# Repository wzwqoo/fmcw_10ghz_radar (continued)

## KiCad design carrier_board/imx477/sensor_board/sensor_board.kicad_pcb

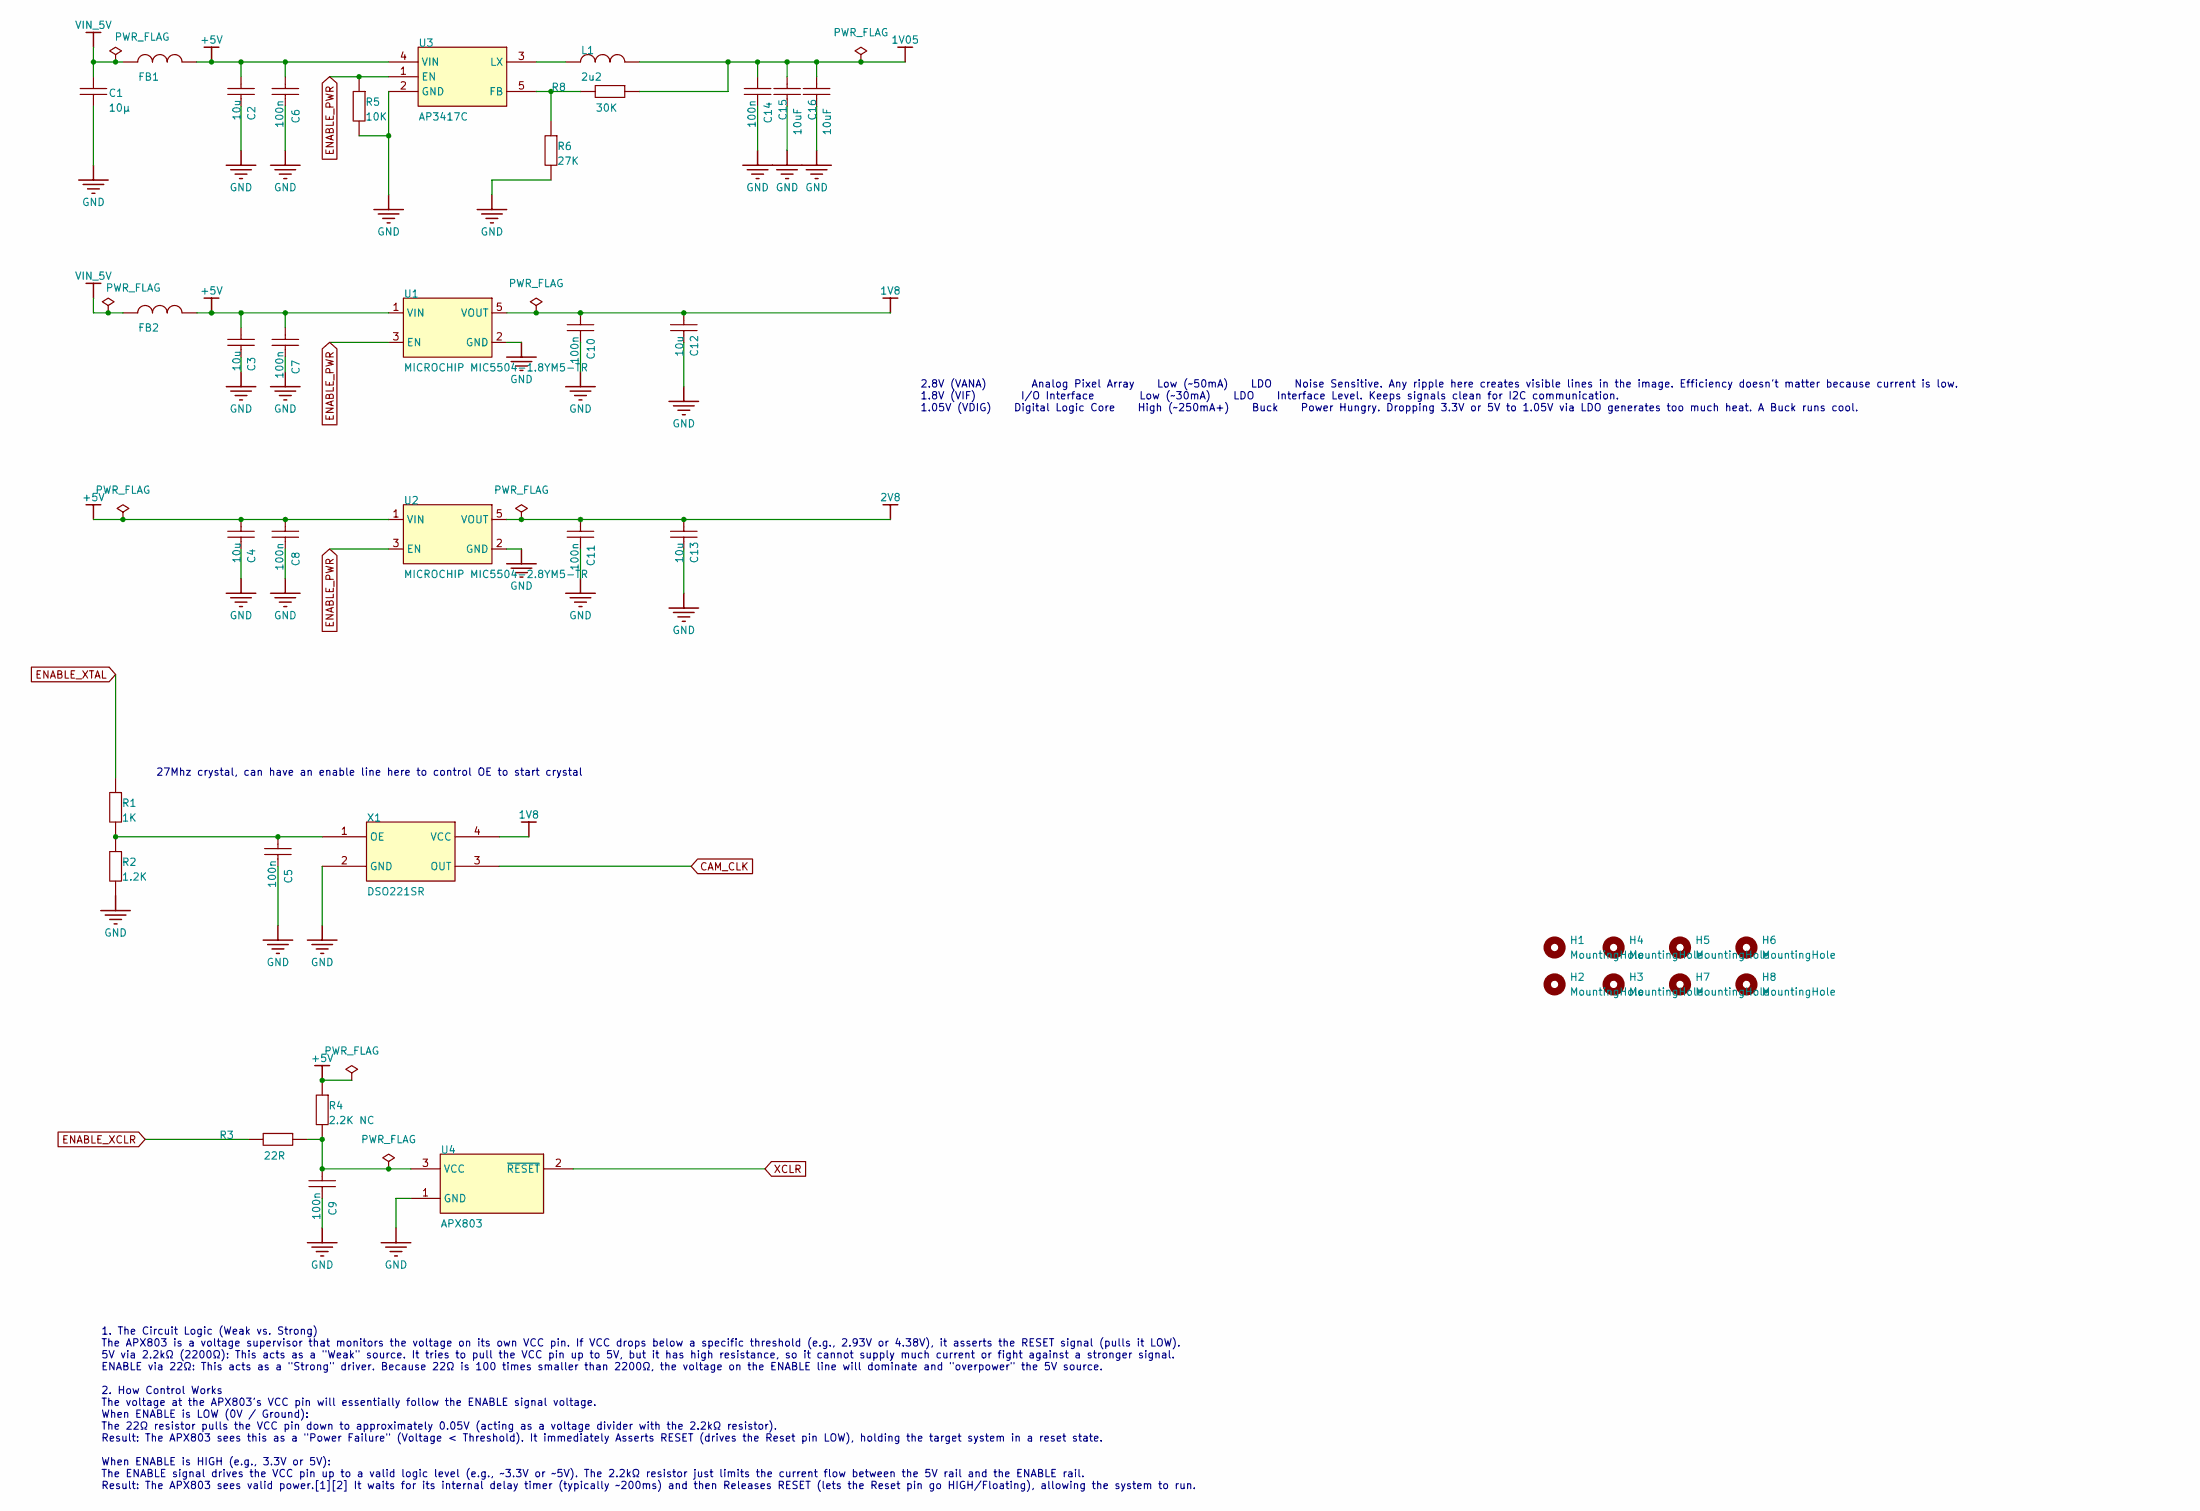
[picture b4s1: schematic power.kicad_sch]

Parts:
C1: 10uF; C_0805_2012Metric; TOLERANCE ±20%; RATINGS 50V; X5R; MANUFACTURER PART NUMBE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 UMK325BJ106MM-T; LCSC Part # C88484
C2, C3, C4, C12, C13: 10uF; C_0805_2012Metric; RATINGS 50V; NP0; VOLTAGE - RATED 50V; MANUFACTURER PART NUMBE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 06035A561JAT2A; LCSC Part # C88484
C5, C6, C7, C8, C9, C10, C11, C14: 100nF; C_0805_2012Metric; TOLERANCE ±10%; RATINGS 16V; X7R; MANUFACTURER PART NUMBE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 CC0402KRX7R7BB103; LCSC Part # C49678
C15, C16: 10uF; C_0805_2012Metric; TOLERANCE ±10%; RATINGS 16V; X5R; MANUFACTURER PART NUMBE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 EMK212BJ475KG-T; LCSC Part # C88484
FB1, FB2: 1 kΩ @ 100 MHz; L_0805_2012Metric; Part# MPZ2012S102AT000; LCSC Part # C76817
H1, H2, H3, H4, H5, H6, H7, H8: MountingHole; MountingHole_2.5mm
L1: 2u2; L_Taiyo-Yuden_MD-4040; Part# CMLO0420H2R2MTT; LCSC Part # C438930
R1: 1K; R_0805_2012Metric; RATINGS 1/16 W; TOLERANCE ±5%; MANUFACTURER PART NUMBE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 RC0402JR-073K3L; LCSC Part # C95781
R2: 1.2K; R_0805_2012Metric; RATINGS 1/16 W; TOLERANCE ±5%; MANUFACTURER PART NUMBE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 RC0402JR-073K3L; LCSC Part # C114526
R3: 22; R_0805_2012Metric; RATINGS 1/16 W; TOLERANCE ±5%; MANUFACTURER PART NUMBE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 RC0402JR-073K3L; LCSC Part # C107702
R4: 2.2K; R_0805_2012Metric; RATINGS 1/16 W; TOLERANCE ±5%; MANUFACTURER PART NUMBE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 RC0402JR-073K3L; LCSC Part # C114237
R5: 10K; R_0805_2012Metric; RATINGS 1/16 W; TOLERANCE ±5%; MANUFACTURER PART NUMBE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 RC0402JR-073K3L; LCSC Part # C100047
R6: 27K; R_0805_2012Metric; RATINGS 1/16 W; TOLERANCE ±5%; MANUFACTURER PART NUMBE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 RC0402JR-073K3L; LCSC Part # C728647
R8: 30K; R_0805_2012Metric; RATINGS 1/16 W; TOLERANCE ±5%; MANUFACTURER PART NUMBE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 RC0402JR-073K3L; LCSC Part # C126352
U1: MICROCHIP MIC5504-1.8YM5-TR; SOT-23-5; Part# MIC5504-1.8YM5-TR; LCSC Part # C626116
U2: MICROCHIP MIC5504-2.8YM5-TR; SOT-23-5; Part# MIC5504-2.8YM5-TR; LCSC Part # C95749
U3: AP3417C; SOT-23-5; Part# AP3417CKTR-G1; LCSC Part # C500759
U4: APX803; SOT-23-3; Part# APX803S-23SA-7; LCSC Part # C2067713
X1: DSO221SR; Crystal_SMD_2520-4Pin_2.5x2.0mm

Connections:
1V05: C14.2, C15.1, C16.1, L1.2, R8.2; also elsewhere on the board
1V8: C10.2, C12.1, U1.5 (VOUT), X1.4 (VCC); also elsewhere on the board
2V8: C11.2, C13.1, U2.5 (VOUT); also elsewhere on the board
+5V: C2.1, C3.1, C4.1, C6.2, C7.2, C8.2, FB1.2, FB2.2, R4.2, U1.1 (VIN), U2.1 (VIN), U3.4 (VIN)
CAM_CLK: X1.3 (OUT); also elsewhere on the board
ENABLE_PWR: R5.2, U1.3 (EN), U2.3 (EN), U3.1 (EN); also elsewhere on the board
ENABLE_XCLR: R3.1; also elsewhere on the board
ENABLE_XTAL: R1.2; also elsewhere on the board
GND: C1.2, C2.2, C3.2, C4.2, C5.1, C6.1, C7.1, C8.1, C9.1, C10.1, C11.1, C12.2, C13.2, C14.1, C15.2, C16.2, R2.1, R5.1, R6.1, U1.2 (GND), U2.2 (GND), U3.2 (GND), U4.1 (GND), X1.2 (GND); also elsewhere on the board
unnamed: R6.2, R8.1, U3.5 (FB)
unnamed: L1.1, U3.3 (LX)
unnamed: C9.2, R3.2, R4.1, U4.3 (VCC)
unnamed: C5.2, R1.1, R2.2, X1.1 (OE)
VIN_5V: C1.1, FB1.1, FB2.1; also elsewhere on the board
XCLR: U4.2 (~RESET); also elsewhere on the board

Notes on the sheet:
1. The Circuit Logic (Weak vs. Strong) The APX803 is a voltage supervisor that monitors the voltage on its own VCC pin. If VCC drops below a specific threshold (e.g., 2.93V or 4.38V), it asserts the RESET signal (pulls it LOW). 5V via 2.2kΩ (2200Ω): This acts as a "Weak" source. It tries to pull th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
2.8V (VANA) Analog Pixel Array Low (~50mA) LDO Noise Sensitive. Any ripple here creates visible lines in the image. Efficiency doesn't matter because current is low. 1.8V (VIF) I/O Interface Low (~30mA) LDO Interface Level. Keeps signals clean for I2C communication. 1.05V (VDIG) Digital Logic Core 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
27Mhz crystal, can have an enable line here to control OE to start crystal

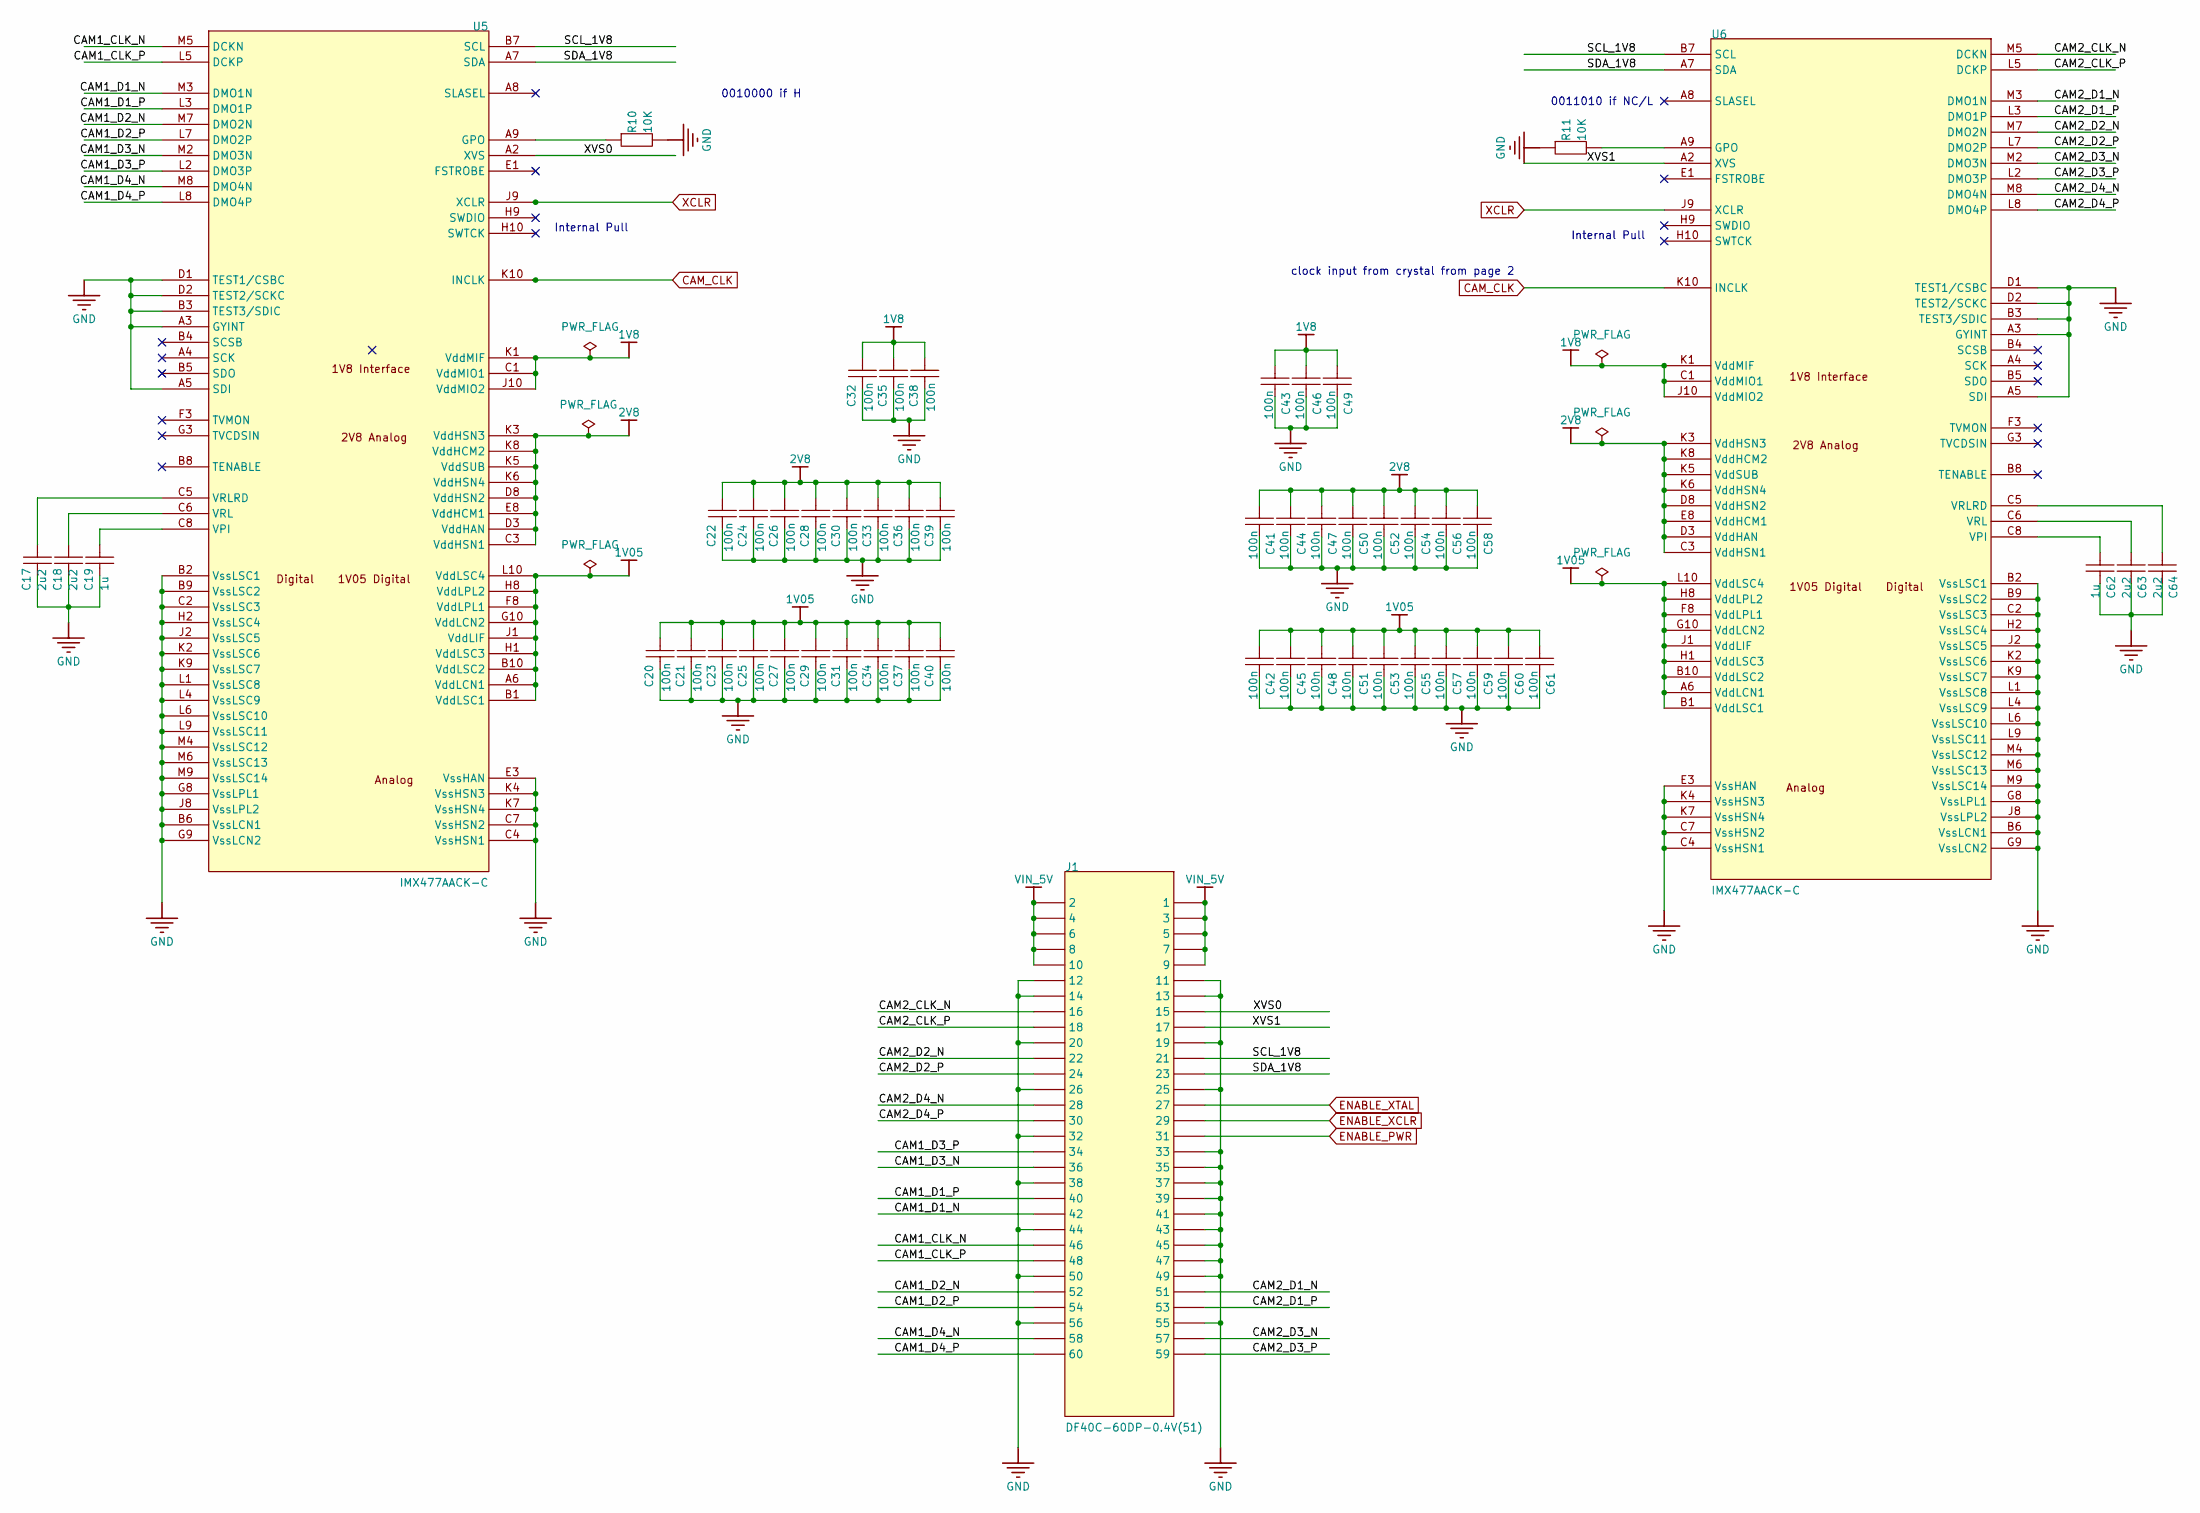
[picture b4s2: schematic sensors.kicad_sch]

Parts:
C17, C18, C19, C62, C63, C64: 10uF; C_0805_2012Metric; RATINGS 50V; NP0; VOLTAGE - RATED 50V; MANUFACTURER PART NUMBE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 06035A561JAT2A; LCSC Part # C88484
C20, C21, C22, C23, C24, C25, C26, C27, C28, C29, C30, C31, C32, C33, C34, C35, C36, C37, C38, C39, C40, C41, C42, C43, C44, C45, C46, C47, C48, C49, C50, C51, C52, C53, C54, C55, C56, C57, C58, C59, C60, C61: 100nF; C_0805_2012Metric; TOLERANCE ±10%; RATINGS 16V; X7R; MANUFACTURER PART NUMBE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 CC0402KRX7R7BB103; LCSC Part # C49678
J1: DF40C-60DP-0.4V(51); Hirose_DF40C-60DP-0.4V_2x30-1MP_P0.4mm; Part# DF40C-60DP-0.4V(51); LCSC Part # C424647
R10, R11: 10K; R_0805_2012Metric; RATINGS 1/16 W; TOLERANCE ±5%; MANUFACTURER PART NUMBE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 RC0402JR-073K3L; LCSC Part # C100047
U5, U6: IMX477AACK-C; LGA-92_L10.5-W8.5-P0.80_IMX477-AAPK-C

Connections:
1V05: C20.2, C21.2, C23.2, C25.2, C27.2, C29.2, C31.2, C34.2, C37.2, C40.2, C42.2, C45.2, C48.2, C51.2, C53.2, C55.2, C57.2, C59.2, C60.2, C61.2, U5.A6 (VddLCN1), U5.B1 (VddLSC1), U5.B10 (VddLSC2), U5.F8 (VddLPL1), U5.G10 (VddLCN2), U5.H1 (VddLSC3), U5.H8 (VddLPL2), U5.J1 (VddLIF), U5.L10 (VddLSC4), U6.A6 (VddLCN1), U6.B1 (VddLSC1), U6.B10 (VddLSC2), U6.F8 (VddLPL1), U6.G10 (VddLCN2), U6.H1 (VddLSC3), U6.H8 (VddLPL2), U6.J1 (VddLIF), U6.L10 (VddLSC4); also elsewhere on the board
1V8: C32.2, C35.2, C38.2, C43.2, C46.2, C49.2, U5.C1 (VddMIO1), U5.J10 (VddMIO2), U5.K1 (VddMIF), U6.C1 (VddMIO1), U6.J10 (VddMIO2), U6.K1 (VddMIF); also elsewhere on the board
2V8: C22.2, C24.2, C26.2, C28.2, C30.2, C33.2, C36.2, C39.2, C41.2, C44.2, C47.2, C50.2, C52.2, C54.2, C56.2, C58.2, U5.C3 (VddHSN1), U5.D3 (VddHAN), U5.D8 (VddHSN2), U5.E8 (VddHCM1), U5.K3 (VddHSN3), U5.K5 (VddSUB), U5.K6 (VddHSN4), U5.K8 (VddHCM2), U6.C3 (VddHSN1), U6.D3 (VddHAN), U6.D8 (VddHSN2), U6.E8 (VddHCM1), U6.K3 (VddHSN3), U6.K5 (VddSUB), U6.K6 (VddHSN4), U6.K8 (VddHCM2); also elsewhere on the board
/sensors/CAM1_CLK_N: J1.46, U5.M5 (DCKN)
/sensors/CAM1_CLK_P: J1.48, U5.L5 (DCKP)
/sensors/CAM1_D1_N: J1.42, U5.M3 (DMO1N)
/sensors/CAM1_D1_P: J1.40, U5.L3 (DMO1P)
/sensors/CAM1_D2_N: J1.52, U5.M7 (DMO2N)
/sensors/CAM1_D2_P: J1.54, U5.L7 (DMO2P)
/sensors/CAM1_D3_N: J1.36, U5.M2 (DMO3N)
/sensors/CAM1_D3_P: J1.34, U5.L2 (DMO3P)
/sensors/CAM1_D4_N: J1.58, U5.M8 (DMO4N)
/sensors/CAM1_D4_P: J1.60, U5.L8 (DMO4P)
/sensors/CAM2_CLK_N: J1.16, U6.M5 (DCKN)
/sensors/CAM2_CLK_P: J1.18, U6.L5 (DCKP)
/sensors/CAM2_D1_N: J1.51, U6.M3 (DMO1N)
/sensors/CAM2_D1_P: J1.53, U6.L3 (DMO1P)
/sensors/CAM2_D2_N: J1.22, U6.M7 (DMO2N)
/sensors/CAM2_D2_P: J1.24, U6.L7 (DMO2P)
/sensors/CAM2_D3_N: J1.57, U6.M2 (DMO3N)
/sensors/CAM2_D3_P: J1.59, U6.L2 (DMO3P)
/sensors/CAM2_D4_N: J1.28, U6.M8 (DMO4N)
/sensors/CAM2_D4_P: J1.30, U6.L8 (DMO4P)
/sensors/SCL_1V8: J1.21, U5.B7 (SCL), U6.B7 (SCL)
/sensors/SDA_1V8: J1.23, U5.A7 (SDA), U6.A7 (SDA)
/sensors/XVS0: J1.15, U5.A2 (XVS)
/sensors/XVS1: J1.17, U6.A2 (XVS)
CAM_CLK: U5.K10 (INCLK), U6.K10 (INCLK); also elsewhere on the board
ENABLE_PWR: J1.31; also elsewhere on the board
ENABLE_XCLR: J1.29; also elsewhere on the board
ENABLE_XTAL: J1.27; also elsewhere on the board
GND: C17.2, C18.2, C19.2, C20.1, C21.1, C22.1, C23.1, C24.1, C25.1, C26.1, C27.1, C28.1, C29.1, C30.1, C31.1, C32.1, C33.1, C34.1, C35.1, C36.1, C37.1, C38.1, C39.1, C40.1, C41.1, C42.1, C43.1, C44.1, C45.1, C46.1, C47.1, C48.1, C49.1, C50.1, C51.1, C52.1, C53.1, C54.1, C55.1, C56.1, C57.1, C58.1, C59.1, C60.1, C61.1, C62.2, C63.2, C64.2, J1.11, J1.12, J1.13, J1.14, J1.19, J1.20, J1.25, J1.26, J1.32, J1.33, J1.35, J1.37, J1.38, J1.39, J1.41, J1.43, J1.44, J1.45, J1.47, J1.49, J1.50, J1.55, J1.56, R10.1, R11.2, U5.A3 (GYINT), U5.A5 (SDI), U5.B2 (VssLSC1), U5.B3 (TEST3/SDIC), U5.B6 (VssLCN1), U5.B9 (VssLSC2), U5.C2 (VssLSC3), U5.C4 (VssHSN1), U5.C7 (VssHSN2), U5.D1 (TEST1/CSBC), U5.D2 (TEST2/SCKC), U5.E3 (VssHAN), U5.G8 (VssLPL1), U5.G9 (VssLCN2), U5.H2 (VssLSC4), U5.J2 (VssLSC5), U5.J8 (VssLPL2), U5.K2 (VssLSC6), U5.K4 (VssHSN3), U5.K7 (VssHSN4), U5.K9 (VssLSC7), U5.L1 (VssLSC8), U5.L4 (VssLSC9), U5.L6 (VssLSC10), U5.L9 (VssLSC11), U5.M4 (VssLSC12), U5.M6 (VssLSC13), U5.M9 (VssLSC14), U6.A3 (GYINT), U6.A5 (SDI), U6.B2 (VssLSC1), U6.B3 (TEST3/SDIC), U6.B6 (VssLCN1), U6.B9 (VssLSC2), U6.C2 (VssLSC3), U6.C4 (VssHSN1), U6.C7 (VssHSN2), U6.D1 (TEST1/CSBC), U6.D2 (TEST2/SCKC), U6.E3 (VssHAN), U6.G8 (VssLPL1), U6.G9 (VssLCN2), U6.H2 (VssLSC4), U6.J2 (VssLSC5), U6.J8 (VssLPL2), U6.K2 (VssLSC6), U6.K4 (VssHSN3), U6.K7 (VssHSN4), U6.K9 (VssLSC7), U6.L1 (VssLSC8), U6.L4 (VssLSC9), U6.L6 (VssLSC10), U6.L9 (VssLSC11), U6.M4 (VssLSC12), U6.M6 (VssLSC13), U6.M9 (VssLSC14); also elsewhere on the board
unnamed: R10.2, U5.A9 (GPO)
unnamed: C19.1, U5.C8 (VPI)
unnamed: C18.1, U5.C6 (VRL)
unnamed: C17.1, U5.C5 (VRLRD)
unnamed: R11.1, U6.A9 (GPO)
unnamed: C62.1, U6.C8 (VPI)
unnamed: C63.1, U6.C6 (VRL)
unnamed: C64.1, U6.C5 (VRLRD)
VIN_5V: J1.1, J1.2, J1.3, J1.4, J1.5, J1.6, J1.7, J1.8, J1.9, J1.10; also elsewhere on the board
XCLR: U5.J9 (XCLR), U6.J9 (XCLR); also elsewhere on the board

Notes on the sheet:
clock input from crystal from page 2
Internal Pull
0011010 if NC/L
0010000 if H

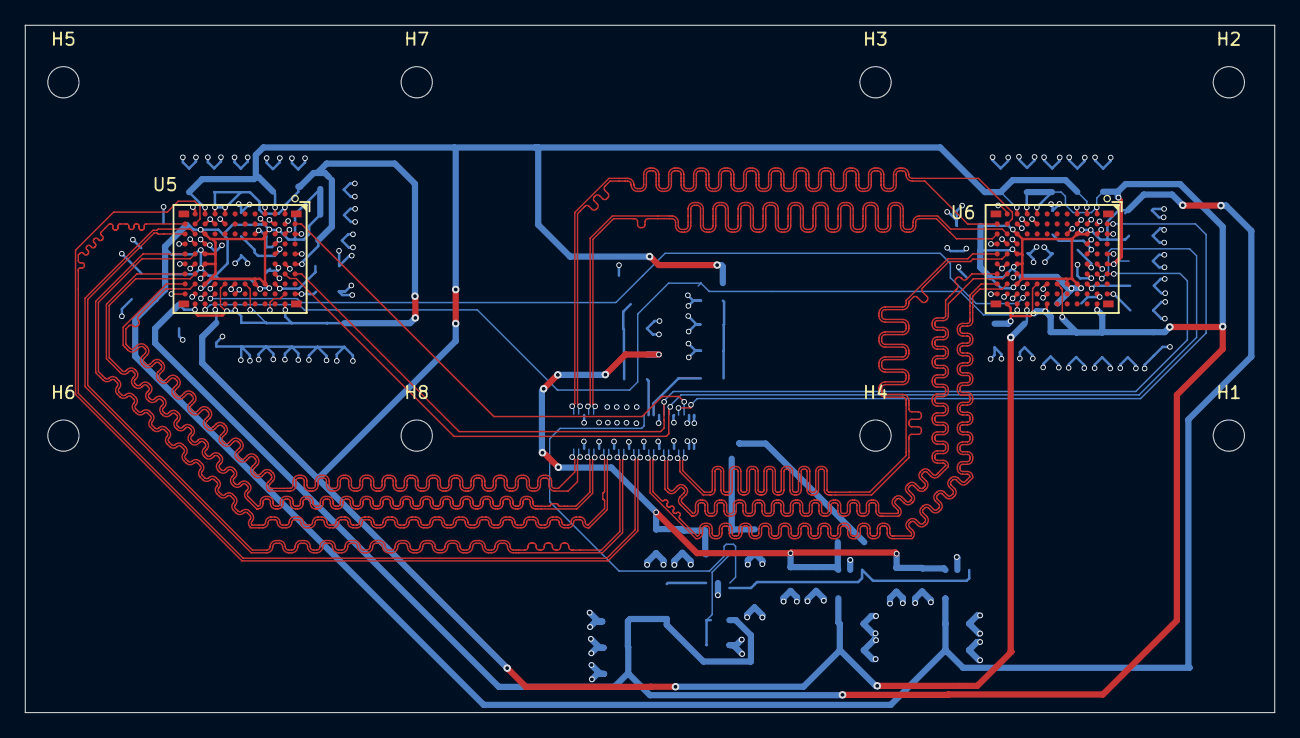
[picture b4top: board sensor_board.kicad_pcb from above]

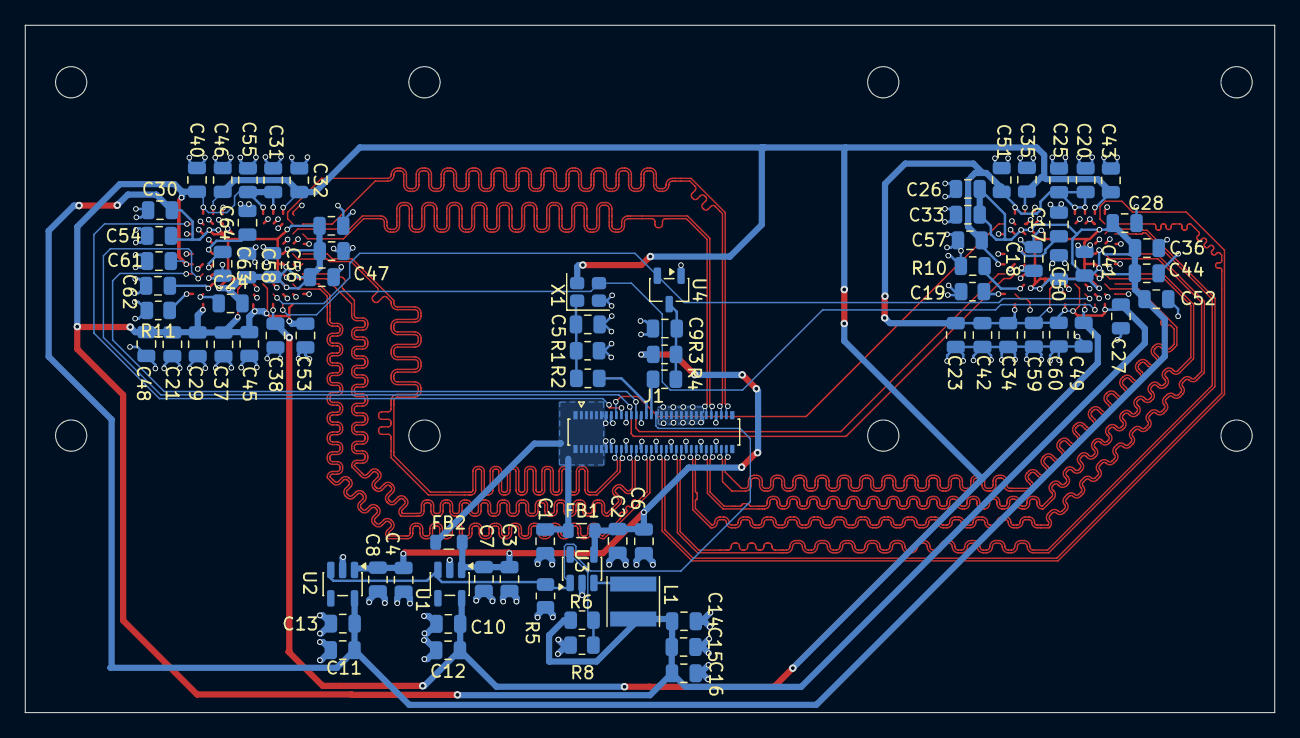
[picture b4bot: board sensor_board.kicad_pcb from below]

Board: 4 copper layers, 100.0 x 55.0 mm, 92 parts (82 on the bottom side), 47 nets.

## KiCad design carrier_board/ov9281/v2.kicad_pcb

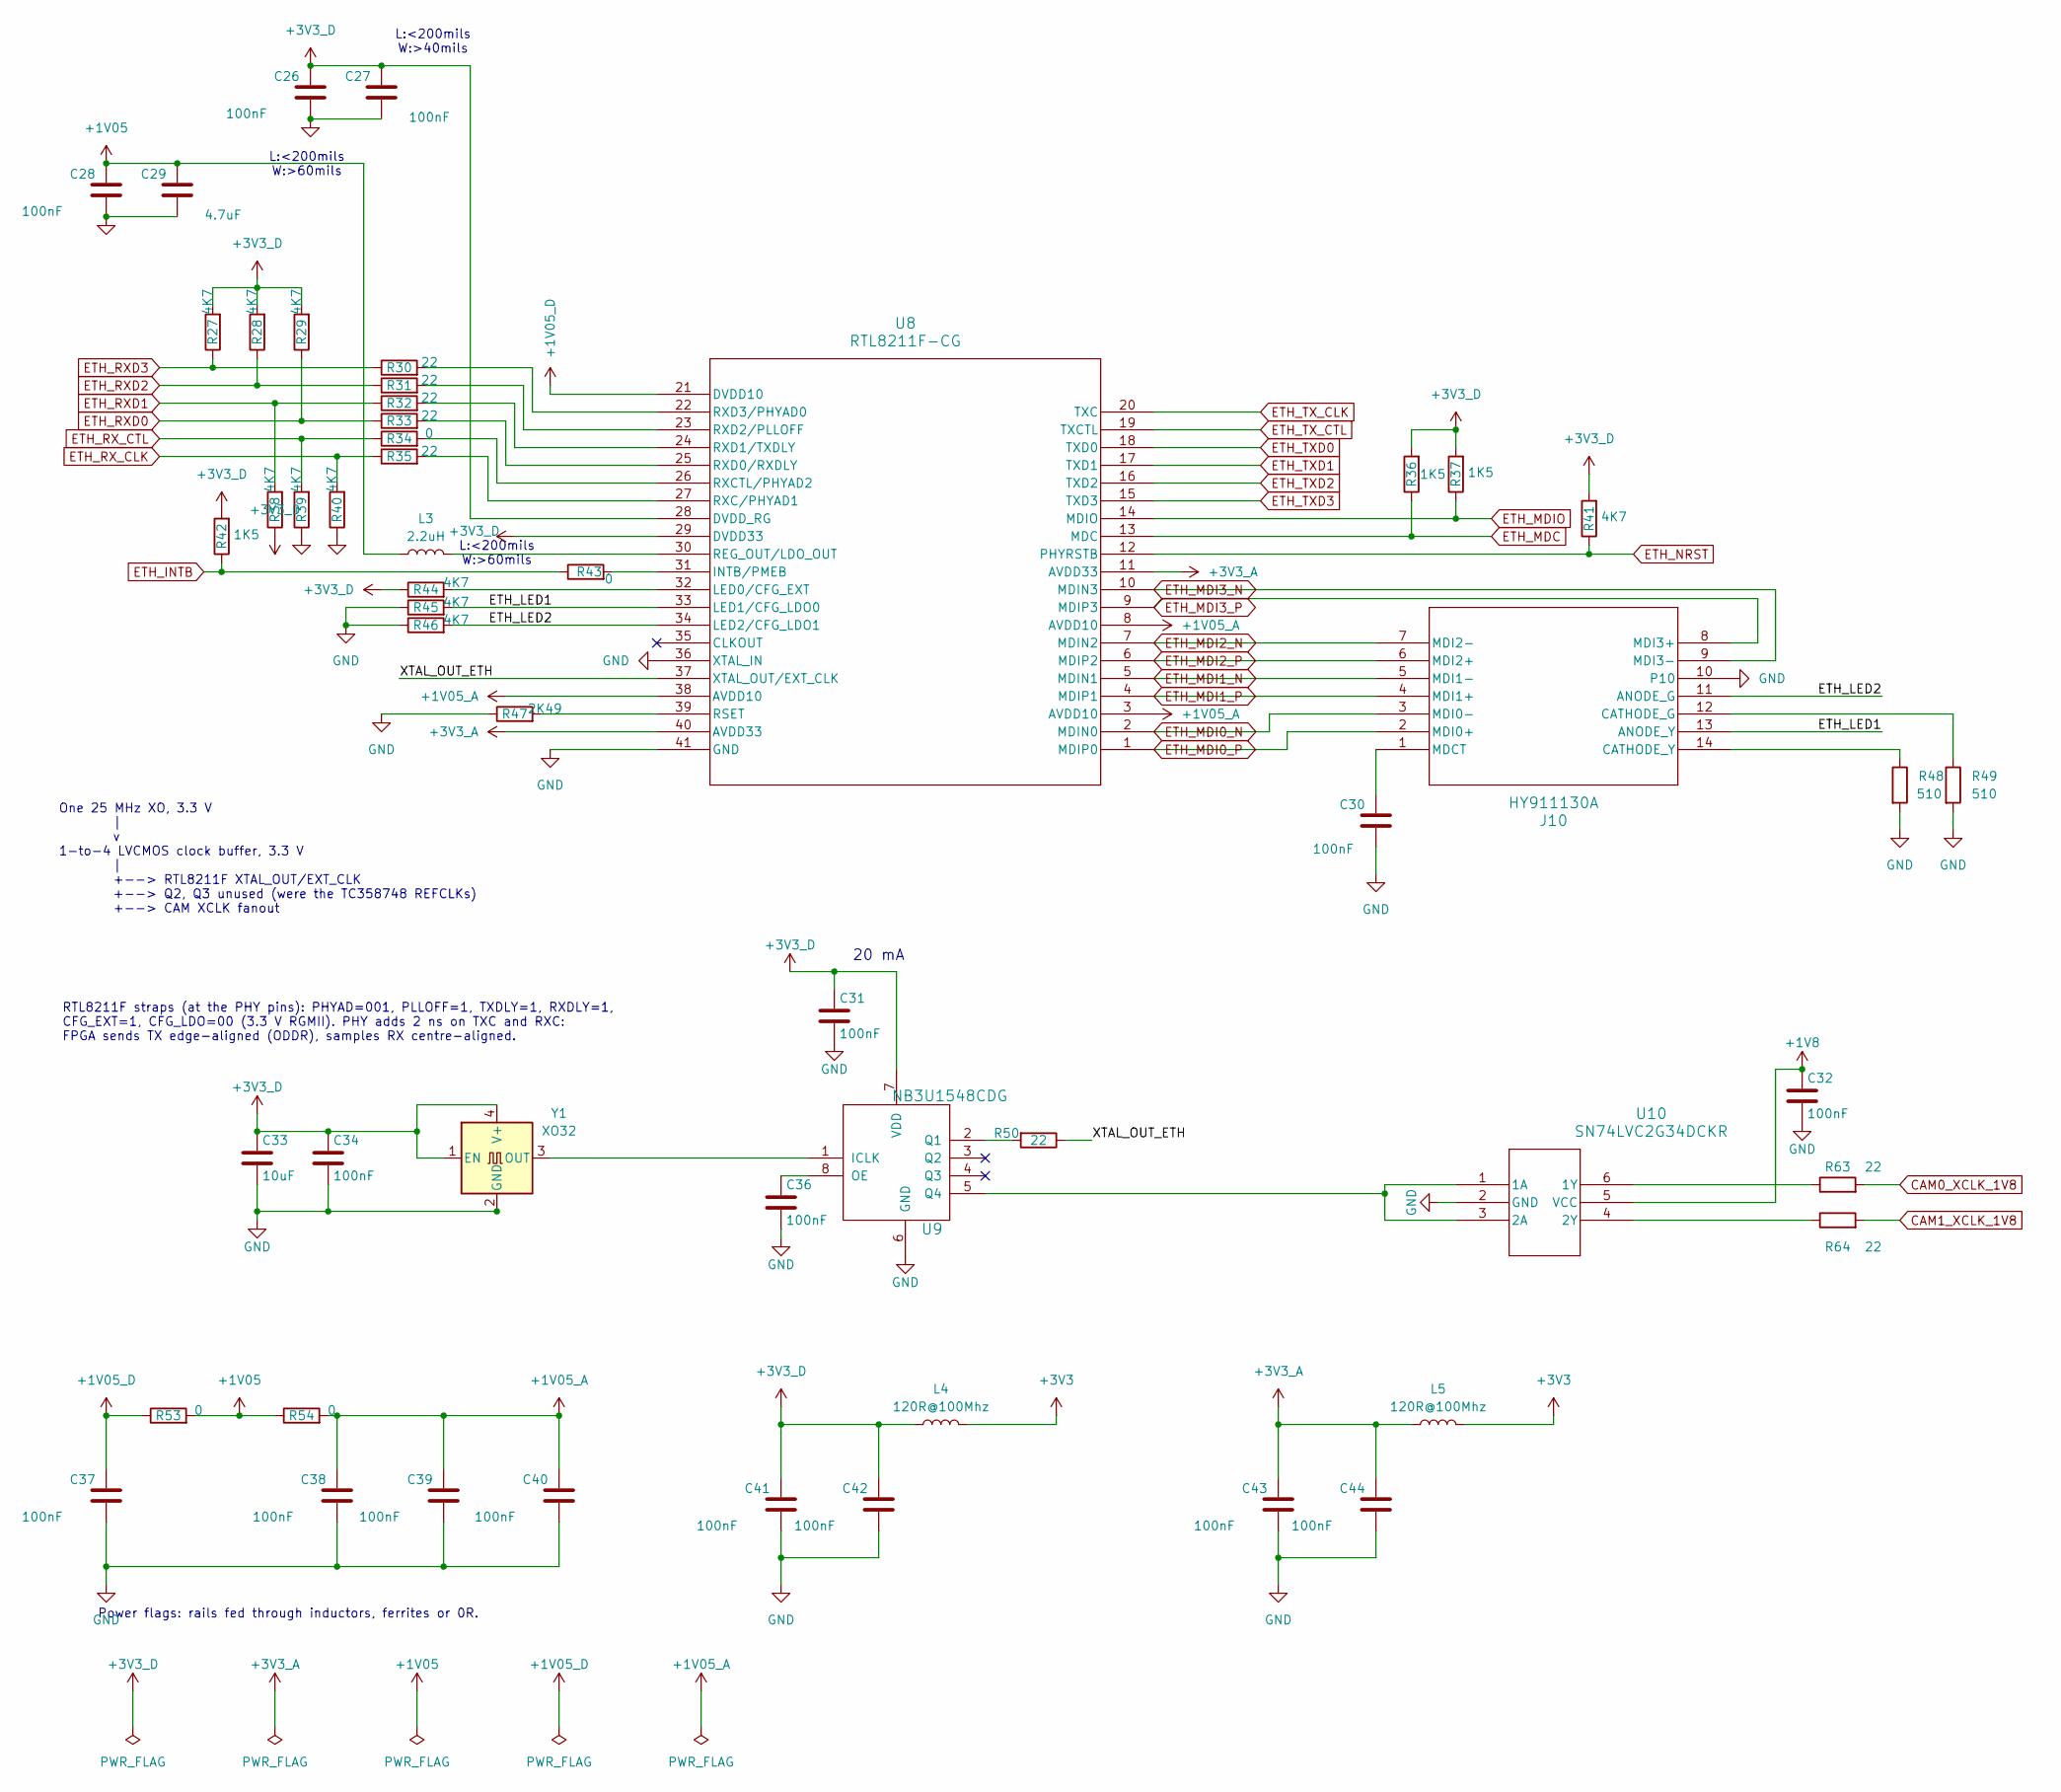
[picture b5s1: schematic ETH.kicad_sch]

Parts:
C26, C27, C28, C30, C31, C32, C34, C36, C37, C40, C41, C42, C43, C44: 100nF; C_0805_2012Metric; Part# x; LCSC Part # x
C29: 4.7uF; C_0805_2012Metric; Part# CC0805KKX7R8BB475; LCSC Part # C354262
C33: 10uF; C_0805_2012Metric; Part# CC0805KKX5R8BB106; LCSC Part # C89831
C38, C39: 100nF; C_0402_1005Metric; Part# x; LCSC Part # x
J10: HY911130A; HY911130A_HAN; LCSC Part # C55679
L3: 2.2uH; L_0805_2012Metric; Part# MLP2012H2R2MT0S1; LCSC Part # C383369
L4, L5: 120R@100Mhz; L_0805_2012Metric; Part# UPZ2012E121-4R0TF; LCSC Part # C97001
R27, R28, R29, R38, R39, R40: 4K7; R_0402_1005Metric; Part# x; LCSC Part # x
R30, R31, R32, R33, R35: 22; R_0402_1005Metric; Part# RC0402FR-0722RL
R34: 0; R_0402_1005Metric; Part# RC0402JR-070RL
R36, R37, R42: 1K5; R_0805_2012Metric; Part# RC0805FR-071K5L; LCSC Part # C114555
R41, R44, R45, R46: 4K7; R_0805_2012Metric; Part# x; LCSC Part # x
R43, R53, R54: 0; R_0805_2012Metric; Part# RC0805JR-070RL; LCSC Part # C96345
R47: 2K49; R_0805_2012Metric; Part# AC0805FR-7W2K49L; LCSC Part # C727992
R48, R49: 510; R_0805_2012Metric; Part# RC0805FR-07510RL; LCSC Part # C114563
R50: 22; R_0805_2012Metric; Part# RC0805JR-0722RL; LCSC Part # C108406
R63, R64: 22; R_0805_2012Metric
U8: RTL8211F-CG; RTL8211F-CG_QFN40_EP3.5; LCSC Part # C187932
U9: NB3U1548CDG; SOIC-8_3.9x4.9mm_P1.27mm; LCSC Part # C603365
U10: SN74LVC2G34DCKR; SOT-363_SC-70-6; LCSC Part # C14461
Y1: XO32; Oscillator_SMD_EuroQuartz_XO32-4Pin_3.2x2.5mm; Part# OT322525MJBA4SL; LCSC Part # C669088

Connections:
+1V05: C28.1, C29.1, L3.1, R53.2, R54.1
+1V05_A: C38.1, C39.1, C40.1, R54.2, U8.3 (AVDD10), U8.8 (AVDD10), U8.38 (AVDD10)
+1V05_D: C37.1, R53.1, U8.21 (DVDD10)
+1V8: C32.1, U10.5 (VCC); also elsewhere on the board
+3V3: L4.2, L5.2; also elsewhere on the board
+3V3_A: C43.1, C44.1, L5.1, U8.11 (AVDD33), U8.40 (AVDD33)
+3V3_D: C26.1, C27.1, C31.1, C33.1, C34.1, C41.1, C42.1, L4.1, R27.2, R28.2, R29.2, R36.2, R37.2, R38.1, R41.2, R42.2, R44.1, U8.28 (DVDD_RG), U8.29 (DVDD33), U9.7 (VDD), Y1.1 (EN), Y1.4 (V+)
/ETH/ETH_LED1: J10.13 (ANODE_Y), R45.2, U8.33 (LED1/CFG_LDO0)
/ETH/ETH_LED2: J10.11 (ANODE_G), R46.2, U8.34 (LED2/CFG_LDO1)
/ETH/XTAL_OUT_ETH: R50.1, U8.37 (XTAL_OUT/EXT_CLK)
CAM0_XCLK_1V8: R63.2; also elsewhere on the board
CAM1_XCLK_1V8: R64.2; also elsewhere on the board
ETH_INTB: R42.1, R43.1; also elsewhere on the board
ETH_MDC: R36.1, U8.13 (MDC); also elsewhere on the board
ETH_MDI0_N: J10.3 (MDI0-), U8.2 (MDIN0)
ETH_MDI0_P: J10.2 (MDI0+), U8.1 (MDIP0)
ETH_MDI1_N: J10.5 (MDI1-), U8.5 (MDIN1)
ETH_MDI1_P: J10.4 (MDI1+), U8.4 (MDIP1)
ETH_MDI2_N: J10.7 (MDI2-), U8.7 (MDIN2)
ETH_MDI2_P: J10.6 (MDI2+), U8.6 (MDIP2)
ETH_MDI3_N: J10.9 (MDI3-), U8.10 (MDIN3)
ETH_MDI3_P: J10.8 (MDI3+), U8.9 (MDIP3)
ETH_MDIO: R37.1, U8.14 (MDIO); also elsewhere on the board
ETH_NRST: R41.1, U8.12 (PHYRSTB); also elsewhere on the board
ETH_RXD0: R29.1, R33.1; also elsewhere on the board
ETH_RXD1: R32.1, R38.2; also elsewhere on the board
ETH_RXD2: R28.1, R31.1; also elsewhere on the board
ETH_RXD3: R27.1, R30.1; also elsewhere on the board
ETH_RX_CLK: R35.1, R40.2; also elsewhere on the board
ETH_RX_CTL: R34.1, R39.2; also elsewhere on the board
ETH_TXD0: U8.18 (TXD0); also elsewhere on the board
ETH_TXD1: U8.17 (TXD1); also elsewhere on the board
ETH_TXD2: U8.16 (TXD2); also elsewhere on the board
ETH_TXD3: U8.15 (TXD3); also elsewhere on the board
ETH_TX_CLK: U8.20 (TXC); also elsewhere on the board
ETH_TX_CTL: U8.19 (TXCTL); also elsewhere on the board
GND: C26.2, C27.2, C28.2, C29.2, C30.2, C31.2, C32.2, C33.2, C34.2, C36.2, C37.2, C38.2, C39.2, C40.2, C41.2, C42.2, C43.2, C44.2, J10.10, R39.1, R40.1, R45.1, R46.1, R47.1, R48.2, R49.2, U8.36 (XTAL_IN), U8.41 (GND), U9.6 (GND), U10.2 (GND), Y1.2 (GND); also elsewhere on the board
unnamed: J10.12 (CATHODE_G), R49.1
unnamed: J10.14 (CATHODE_Y), R48.1
unnamed: C30.1, J10.1 (MDCT)
unnamed: R43.2, U8.31 (INTB/PMEB)
unnamed: R44.2, U8.32 (LED0/CFG_EXT)
unnamed: L3.2, U8.30 (REG_OUT/LDO_OUT)
unnamed: R47.2, U8.39 (RSET)
unnamed: R34.2, U8.26 (RXCTL/PHYAD2)
unnamed: R35.2, U8.27 (RXC/PHYAD1)
unnamed: R33.2, U8.25 (RXD0/RXDLY)
unnamed: R32.2, U8.24 (RXD1/TXDLY)
unnamed: R31.2, U8.23 (RXD2/PLLOFF)
unnamed: R30.2, U8.22 (RXD3/PHYAD0)
unnamed: U9.1 (ICLK), Y1.3 (OUT)
unnamed: C36.1, U9.8 (OE)
unnamed: R50.2, U9.2 (Q1)
unnamed: U9.5 (Q4), U10.1 (1A), U10.3 (2A)
unnamed: R63.1, U10.6 (1Y)
unnamed: R64.1, U10.4 (2Y)

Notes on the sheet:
L:<200mils W:>40mils
L:<200mils W:>60mils
One 25 MHz XO, 3.3 V | v 1-to-4 LVCMOS clock buffer, 3.3 V | +--> RTL8211F XTAL_OUT/EXT_CLK +--> Q2, Q3 unused (were the TC358748 REFCLKs) +--> CAM XCLK fanout
20 mA
RTL8211F straps (at the PHY pins): PHYAD=001, PLLOFF=1, TXDLY=1, RXDLY=1, CFG_EXT=1, CFG_LDO=00 (3.3 V RGMII). PHY adds 2 ns on TXC and RXC: FPGA sends TX edge-aligned (ODDR), samples RX centre-aligned.
Power flags: rails fed through inductors, ferrites or 0R.

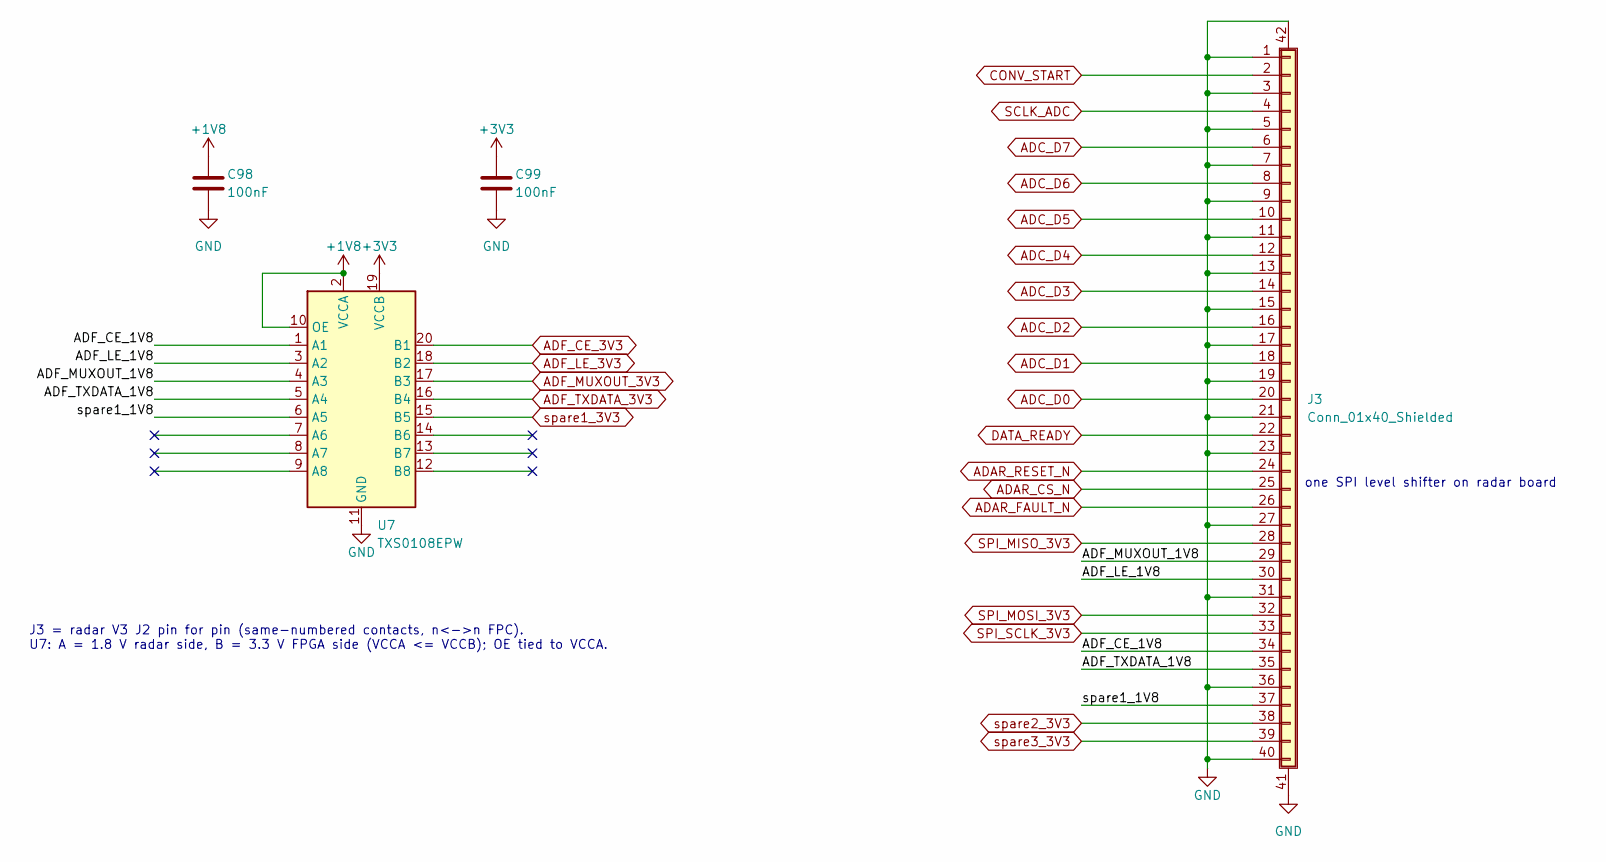
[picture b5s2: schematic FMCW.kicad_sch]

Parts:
C98, C99: 100nF; C_0402_1005Metric
J3: Conn_01x40_Shielded; FPC-SMD_40P-P0.50_XUNPU_FPC-05FB-40PH20; Part# FPC-05FB-40PH20; LCSC Part # C2856837
U7: TXS0108EPW; TSSOP-20_4.4x6.5mm_P0.65mm; LCSC Part # C17206

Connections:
+1V8: C98.1, U7.2 (VCCA), U7.10 (OE); also elsewhere on the board
+3V3: C99.1, U7.19 (VCCB); also elsewhere on the board
/FMCW/ADF_CE_1V8: J3.34, U7.1 (A1)
/FMCW/ADF_LE_1V8: J3.30, U7.3 (A2)
/FMCW/ADF_MUXOUT_1V8: J3.29, U7.4 (A3)
/FMCW/ADF_TXDATA_1V8: J3.35, U7.5 (A4)
/FMCW/spare1_1V8: J3.37, U7.6 (A5)
ADAR_CS_N: J3.25; also elsewhere on the board
ADAR_FAULT_N: J3.26; also elsewhere on the board
ADAR_RESET_N: J3.24; also elsewhere on the board
ADC_D0: J3.20; also elsewhere on the board
ADC_D1: J3.18; also elsewhere on the board
ADC_D2: J3.16; also elsewhere on the board
ADC_D3: J3.14; also elsewhere on the board
ADC_D4: J3.12; also elsewhere on the board
ADC_D5: J3.10; also elsewhere on the board
ADC_D6: J3.8; also elsewhere on the board
ADC_D7: J3.6; also elsewhere on the board
ADF_CE_3V3: U7.20 (B1); also elsewhere on the board
ADF_LE_3V3: U7.18 (B2); also elsewhere on the board
ADF_MUXOUT_3V3: U7.17 (B3); also elsewhere on the board
ADF_TXDATA_3V3: U7.16 (B4); also elsewhere on the board
CONV_START: J3.2; also elsewhere on the board
DATA_READY: J3.22; also elsewhere on the board
GND: C98.2, C99.2, J3.1, J3.3, J3.5, J3.7, J3.9, J3.11, J3.13, J3.15, J3.17, J3.19, J3.21, J3.23, J3.27, J3.31, J3.36, J3.40, J3.41 (Shield), J3.42 (Shield), U7.11 (GND); also elsewhere on the board
SCLK_ADC: J3.4; also elsewhere on the board
SPI_MISO_3V3: J3.28; also elsewhere on the board
SPI_MOSI_3V3: J3.32; also elsewhere on the board
SPI_SCLK_3V3: J3.33; also elsewhere on the board
spare1_3V3: U7.15 (B5); also elsewhere on the board
spare2_3V3: J3.38; also elsewhere on the board
spare3_3V3: J3.39; also elsewhere on the board

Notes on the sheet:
one SPI level shifter on radar board
J3 = radar V3 J2 pin for pin (same-numbered contacts, n<->n FPC). U7: A = 1.8 V radar side, B = 3.3 V FPGA side (VCCA <= VCCB); OE tied to VCCA.
